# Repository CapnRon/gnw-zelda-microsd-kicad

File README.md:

# GnW-Zelda-MicroSD

A castellated-edge microSD interposer for the Game & Watch: The Legend of
Zelda console mod scene -- built as original KiCad artwork, informed by
existing community Gerber-only releases rather than copied from any of
them.

The board mates directly to the console's STM32 mainboard via a
7-position castellated edge (real 0.3x1.2mm SMD pad geometry, machined
flush by the board-edge mill -- this is the critical mechanical/electrical
mating surface, not an approximation) and carries an onboard RT9193-28GB
LDO regulating the console's raw ~4.2V battery rail down to a safe 2.8V
for the microSD card.

**This is a flex PCB**, not rigid: 2-layer, 1oz copper both sides on a
2mil (50.8um) polyimide core, 0.1408mm total board thickness.

## Status

Working draft, not yet fab-verified on real hardware. Electrically clean
(0 unconnected nets, 0 shorts per `kicad-cli pcb drc`) with real routing
and filled ground pours on both copper layers. Remaining DRC output is
DFM-grade (clearances, drill sizes, silk overlap) -- normal manual-review
territory before ordering boards, not electrical faults. See
`docs/design-notes.md` for the full derivation, findings, and everything
still worth double-checking by hand in the KiCad GUI before fabrication.

## Commit history

- **Initial commit** -- the original reconstruction: schematic, PCB,
  footprints, and silkscreen rebuilt from scratch in KiCad from measured
  Gerber geometry (see Origin and attribution below). No third-party
  KiCad source files were used at this point -- every footprint was
  RE'd/approximated by hand from pad positions and sizes read off the
  Gerbers.
- **This commit** -- incorporates real assets from PrimoAngelo's native
  KiCad source (added as source material in the prior commit) now that
  he's confirmed as the known-good original author: J2 (microSD socket)
  and J3 (VBAT tab) were swapped from their RE'd/approximated footprints
  to his real `MSD1A`/`Pad_1x1_5` pad geometry, and a real STEP model was
  wired into U1 (RT9193 LDO). C1/C2/R1 now carry a second, real
  hand-solder-0805 footprint stacked at the same location as their
  original passive footprint, so either package size can be assembled.
  Also fixed a schematic/PCB reference-designator mismatch (J2/J3 and
  U1/U2 were swapped between the two files) and a batch of inconsistent
  net names left over from re-syncing the PCB against the schematic.

## Repository layout

```
hardware/         KiCad project (open GnW-Zelda-MicroSD.kicad_pro here)
production/       Gerbers + drill files (RS-274X, Excellon) + a zipped bundle
docs/             Design notes, top/bottom copper + 3D renders
source-material/  Original third-party source files this design descends
                   from, preserved for attribution/licence compliance --
                   see source-material/README.md
LICENSE           CERN-OHL-S v2 full text
NOTICE.md         Licensing rationale and attribution summary
```

## Circuit

- **U1** -- RT9193-28GB LDO. VIN <- raw battery (~4.2V) via the J1
  castellated edge; EN <- console GPIO (via J1); VOUT -> 2.8V microSD
  supply.
- **J2** -- microSD socket (SPI-mode wiring: CS/MOSI/MISO/CLK + VDD/GND),
  PrimoAngelo's real `MSD1A` footprint.
- **J1** -- 7-position castellated edge: GND, CS, MISO, CLK, MOSI, NC
  (spare), EN.
- **J3** -- castellated VBAT solder tab, PrimoAngelo's real `Pad_1x1_5`
  footprint (same machined-edge technique as J1) -- solders directly to
  the positive terminal of an external SMD capacitor.
- **R1** -- 100k pulldown holding the LDO disabled by default until the
  console GPIO actively enables it. Real hand-solder-0805 footprint
  stacked at the same location as the original RE'd footprint.
- **C1/C2** -- input/output decoupling for U1. Same dual-footprint
  stacking as R1 (0805 hand-solder on top of the original).
- **H1-H4** -- plated, electrically-isolated mounting pads (3.0mm pad /
  1.8mm drill), positioned to match the reference designs' mounting
  pattern.

## Origin and attribution

This design was reconstructed from precise geometry (board outline, pad
positions/sizes, net connectivity, and real copper routing) extracted
directly from Gerber-only community releases for the same G&W Zelda
microSD mod, tracing back through three generations of prior work:

- **Tim Schuerewegen** originated the project.
- **Hundshamer** picked it up and pushed it forward to its final form,
  `GNW-MICROSDx1-ZELDA-V3.4`. Used during reconstruction for
  cross-validation (confirmed identical castellated pinout via a
  different edge-connector pin-numbering scheme than PrimoAngelo's
  release) and as the source for the drilled-via castellation technique
  referenced during development.
- **PrimoAngelo** began his own work from Hundshamer's v3.4 design,
  producing `MicroSD_Zelda_FORO_JLC_FIX_V2 - NO_LOGO`, credited to him in
  its own back-silkscreen (visible in the source Gerbers). This is the
  primary geometric basis for this repo's outline, placement, and
  routing.

Everything in this repository (schematic, PCB, footprints, silkscreen)
was rebuilt from scratch in KiCad from measured geometry, not copied.
This reconstruction was completed before any contact with any of the
above. Afterward, both PrimoAngelo and Hundshamer were reached directly:
PrimoAngelo confirmed authorship and provided native KiCad source for
this design and a sibling Mario board; Hundshamer confirmed the lineage
back to Schuerewegen's original project in a friendly exchange, but had
no additional source material to contribute beyond what was already used
above. All original source material received is preserved under
`source-material/` for full provenance and CERN-OHL-S v2 compliance; see
`source-material/README.md` for the complete attribution chain and
`NOTICE.md` for the licensing rationale. Full credit to the original
designers for the mod itself; if you're one of them and want anything
here changed or removed, open an issue.

## License

CERN-OHL-S v2 (CERN Open Hardware Licence Version 2 - Strongly
Reciprocal). See [LICENSE](LICENSE) and [NOTICE.md](NOTICE.md).

## Building / opening

Requires KiCad 10. Open `hardware/GnW-Zelda-MicroSD.kicad_pro`.

Most custom parts (castellated connectors, exact-geometry footprints for
the LDO/passives) are embedded directly in the `.kicad_pcb`. J2 and J3
now use real footprints from PrimoAngelo's native library, referenced via
project-scoped libraries in `hardware/fp-lib-table` that point into
`source-material/` with `${KIPRJMOD}`-relative paths -- so the project
stays portable to any clone location, but `source-material/` must come
along with it. The schematic symbol library
(`hardware/gnw_zelda_microsd.kicad_sym`) is referenced the same way.

## Before ordering boards

- This is a hand-routed/reconstructed draft -- give it a real pass in the
  KiCad GUI (visual DRC review, silk/courtyard cleanup) before sending to
  a fab.
- The castellated edge geometry is the one dimension that matters most:
  verify pad pitch/size against your actual console board before
  committing to a fab run.
- No BOM/pick-and-place export included yet -- add before ordering
  assembly.

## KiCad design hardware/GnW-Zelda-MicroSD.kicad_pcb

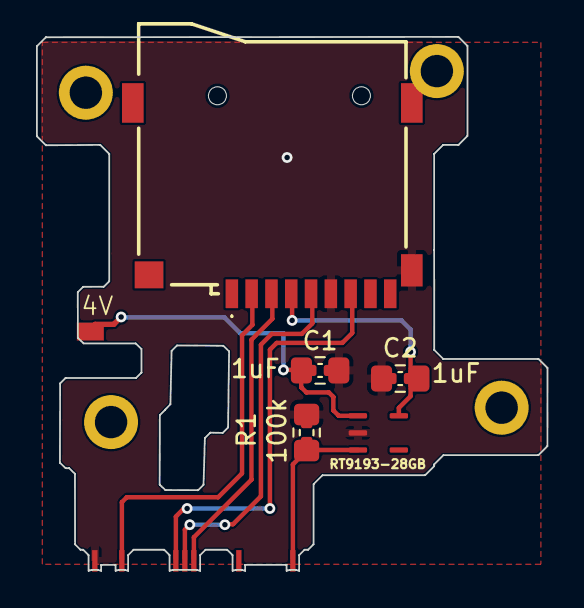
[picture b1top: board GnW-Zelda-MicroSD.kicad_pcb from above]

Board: 2 copper layers, 28.4 x 29.7 mm, 11 parts (0 on the bottom side), 8 nets.

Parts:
C1, C2: 1uF; C_0402_1005Metric
H1, H2, H3, H4: MountingHole_3.0mm; MountingHole_Plated
J1: Castellated_Edge_7P
J2: MicroSD_Socket_TFP09; MSD1A
J3: Battery_Tap_2P; Pad_1x1_5
R1: 100k; R_0402_1005Metric
RT9193-28GB: RT9193-28GB; RT9193_exact

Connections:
EN_PA15: J1.7 (EN), R1.1, RT9193-28GB.3 (EN)
GND: C1.2, C2.2, J1.1 (GND), J2.6 (GND), J2.10 (SHIELD_GND), R1.2, RT9193-28GB.2 (GND)
SPI_CLK: J1.4 (CLK), J2.5 (SCLK)
SPI_CS: J1.2 (CS), J2.2 (CS)
SPI_MISO: J1.3 (MISO), J2.7 (DO)
SPI_MOSI: J1.5 (MOSI), J2.3 (DI)
VBAT_4V2: C1.1, J3.1 (VBAT_1), RT9193-28GB.1 (VIN)
VDD_SD_2V8: C2.1, J2.4 (VDD), RT9193-28GB.5 (VOUT)

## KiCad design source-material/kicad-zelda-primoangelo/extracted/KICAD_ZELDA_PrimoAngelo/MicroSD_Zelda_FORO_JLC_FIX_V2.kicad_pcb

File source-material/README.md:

# Source material

This directory preserves, unmodified, every original design file this
project's attribution chain depends on -- kept here for provenance and
CERN-OHL-S v2 licence compliance (Covered Source must be made available;
see the repository [LICENSE](../LICENSE) and [NOTICE.md](../NOTICE.md)).

Each subdirectory contains the original archive exactly as received
(`*.zip`) plus its extracted contents (`extracted/`) for easier browsing
and diffing.

## Attribution chain

1. **Tim Schuerewegen** originated the Game & Watch Zelda microSD mod
   project this whole lineage descends from.
2. **Hundshamer** picked up the project and pushed it forward to its
   final form, `GNW-MICROSDx1-ZELDA-V3.4` -- see
   `gnw-microsd-zelda-v3.4-hundshamer/`.
3. **PrimoAngelo** began his own work from Hundshamer's v3.4 design,
   producing a derivative/alternate release -- see
   `microsd-zelda-gerbers-primoangelo/` (the Gerber-only file this
   repository was reverse-engineered from) and `kicad-zelda-primoangelo/`
   (PrimoAngelo's own native KiCad source for the same design, obtained
   later).
4. **This repository** was reverse-engineered from PrimoAngelo's
   Gerber-only release, then cross-validated against Hundshamer's v3.4
   design, before any contact with any of the above.

After that reconstruction was complete, both PrimoAngelo and Hundshamer
were contacted directly. PrimoAngelo confirmed authorship and provided
native KiCad source for this design and a sibling Mario board (see
below). Hundshamer confirmed the lineage back to Schuerewegen's original
project in a friendly exchange, but had no additional source material to
contribute beyond `GNW-MICROSDx1-ZELDA-V3.4`, already included here.

## `gnw-microsd-zelda-v3.4-hundshamer/`

`GnW_SD_v2.zip`, containing `GNW-MICROSDx1-ZELDA-V3.4` -- a Gerber/
Excellon-only release by **Hundshamer**, who picked up Tim Schuerewegen's
original Game & Watch Zelda microSD mod project and pushed it forward to
this, its final v3.4 form. Used during the original reverse-engineering
work for cross-validation (it confirmed the castellated pinout via a
different edge-connector pin-numbering scheme than PrimoAngelo's release)
and as the source for the drilled-via castellation technique referenced
in `docs/design-notes.md`.

## `microsd-zelda-gerbers-primoangelo/`

`MicroSD_Zelda_Final.zip`, containing
`MicroSD_Zelda_FORO_JLC_FIX_V2 - NO_LOGO` -- a Gerber/Excellon-only
release (no native KiCad project) credited to **PrimoAngelo** in its own
back-silkscreen, who began his own work from Hundshamer's v3.4 design
above. This is the file this repository's design was originally
reverse-engineered from, before any contact with any of the original
designers -- see `docs/design-notes.md` for the full reverse-engineering
methodology.

## `kicad-zelda-primoangelo/`

`KICAD_ZELDA_PrimoAngelo.zip`, containing the native KiCad project
(`MicroSD_Zelda_FORO_JLC_FIX_V2.kicad_pcb`/`.kicad_pro`) for the same
design above. Provided directly by PrimoAngelo **after** this
repository's reverse-engineering work was already complete, when the
designer was contacted for permission/attribution. Included here for full
provenance and licence compliance; this repository's own KiCad files were
not re-derived from it, since the reconstruction from Gerbers was already
finished and independently verified by the time this arrived.

## `kicad-mario-primoangelo/`

`KICAD_MARIO_PrimoAngelo.zip`, containing a native KiCad project
(`MicroSD_Mario_JLC_FIX_V3.kicad_pcb`/`.kicad_pro`) for a sibling
microSD mod board for a different Game & Watch title (Super Mario Bros.),
also by PrimoAngelo. Provided for the same reason as above, during the
same contact. Not a source for this repository's Zelda board -- included
purely for attribution/provenance and as reference material for anyone
working on the Mario variant in the future.

## `kicad-libs-primoangelo/`

`Libs.zip`, containing PrimoAngelo's own native KiCad footprint libraries
and 3D models used to build the designs above: `Impronte/` ("footprints",
Italian) with `Pad.pretty`/`_FG_Pad.pretty` (the castellated edge-contact
footprints, including `Pad_0_3x1_2.kicad_mod` -- matching this
repository's own independently-reconstructed 0.3x1.2mm castellated pad
geometry exactly, real confirmation the original reverse-engineering in
`docs/design-notes.md` got the geometry right) and `_FG_MicroSD.pretty`
(microSD socket/connector footprints), plus `Modelli_3D/` ("3D models")
with STEP models for the microSD socket and connector. Provided by
PrimoAngelo in a later contact, for the same attribution/provenance
reason as the items above -- not used to modify this repository's
existing (already-verified) footprints, included for completeness and as
a resource for future work (e.g. 3D visualization, mechanical checks).

## Licensing note

These files are third-party work, included here under the terms of
CERN-OHL-S v2 (the licence this repository itself is released under --
see [NOTICE.md](../NOTICE.md)). They are not covered by this repository's
own attribution disclaimers in `README.md`; refer to the original
designers for any use beyond what CERN-OHL-S v2 permits.

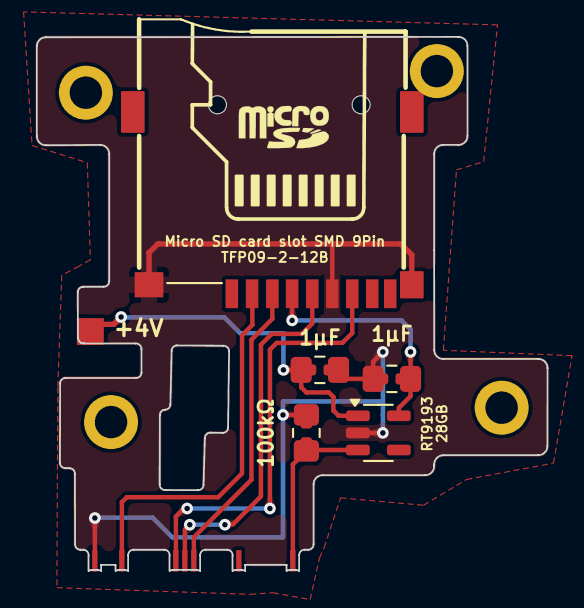
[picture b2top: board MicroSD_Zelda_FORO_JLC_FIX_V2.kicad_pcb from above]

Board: 2 copper layers, 28.4 x 29.7 mm, 21 parts (1 on the bottom side), 8 nets.

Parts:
1µF, 1µF#2: 1u; C_0402_1005Metric_Pad0.74x0.62mm_HandSolder
100kΩ: 100k; R_0402_1005Metric_Pad0.72x0.64mm_HandSolder
C2, C4: 1u; C_0805_2012Metric_Pad1.18x1.45mm_HandSolder
H1, H2, H3, H4: MountingHole; MountingHole_1.7x3mm
J9: TFP09-2-12B
Pin77, Pin83, Pin88, Pin89, Pin90, Pin96, Pin99: PadMicro; Pad_0_3x1_2
R2: 100k; R_0805_2012Metric_Pad1.20x1.40mm_HandSolder
RT9193: RT9193-28GB; SOT-23-5
Ref**: Val**; drawing
Ref**#2: Val**; drawing

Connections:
/CLK: J9.5 (CLK), Pin89.1
/CS: J9.2 (CS), Pin96.1
/EN_LDO: 100kΩ.1, Pin77.1, R2.1, RT9193.3 (EN)
/MISO: J9.7 (MISO), Pin90.1
/MOSI: J9.3 (MOSI), Pin88.1
GND: 1µF.1, 1µF#2.1, 100kΩ.2, C2.1, C4.1, J9.6 (VSS), J9.10 (SHIELD), Pin99.1, R2.2, RT9193.2 (GND)
unnamed: 1µF.2, C2.2, RT9193.1 (IN)
unnamed: 1µF#2.2, C4.2, J9.4 (VDD), RT9193.5 (OUT)
